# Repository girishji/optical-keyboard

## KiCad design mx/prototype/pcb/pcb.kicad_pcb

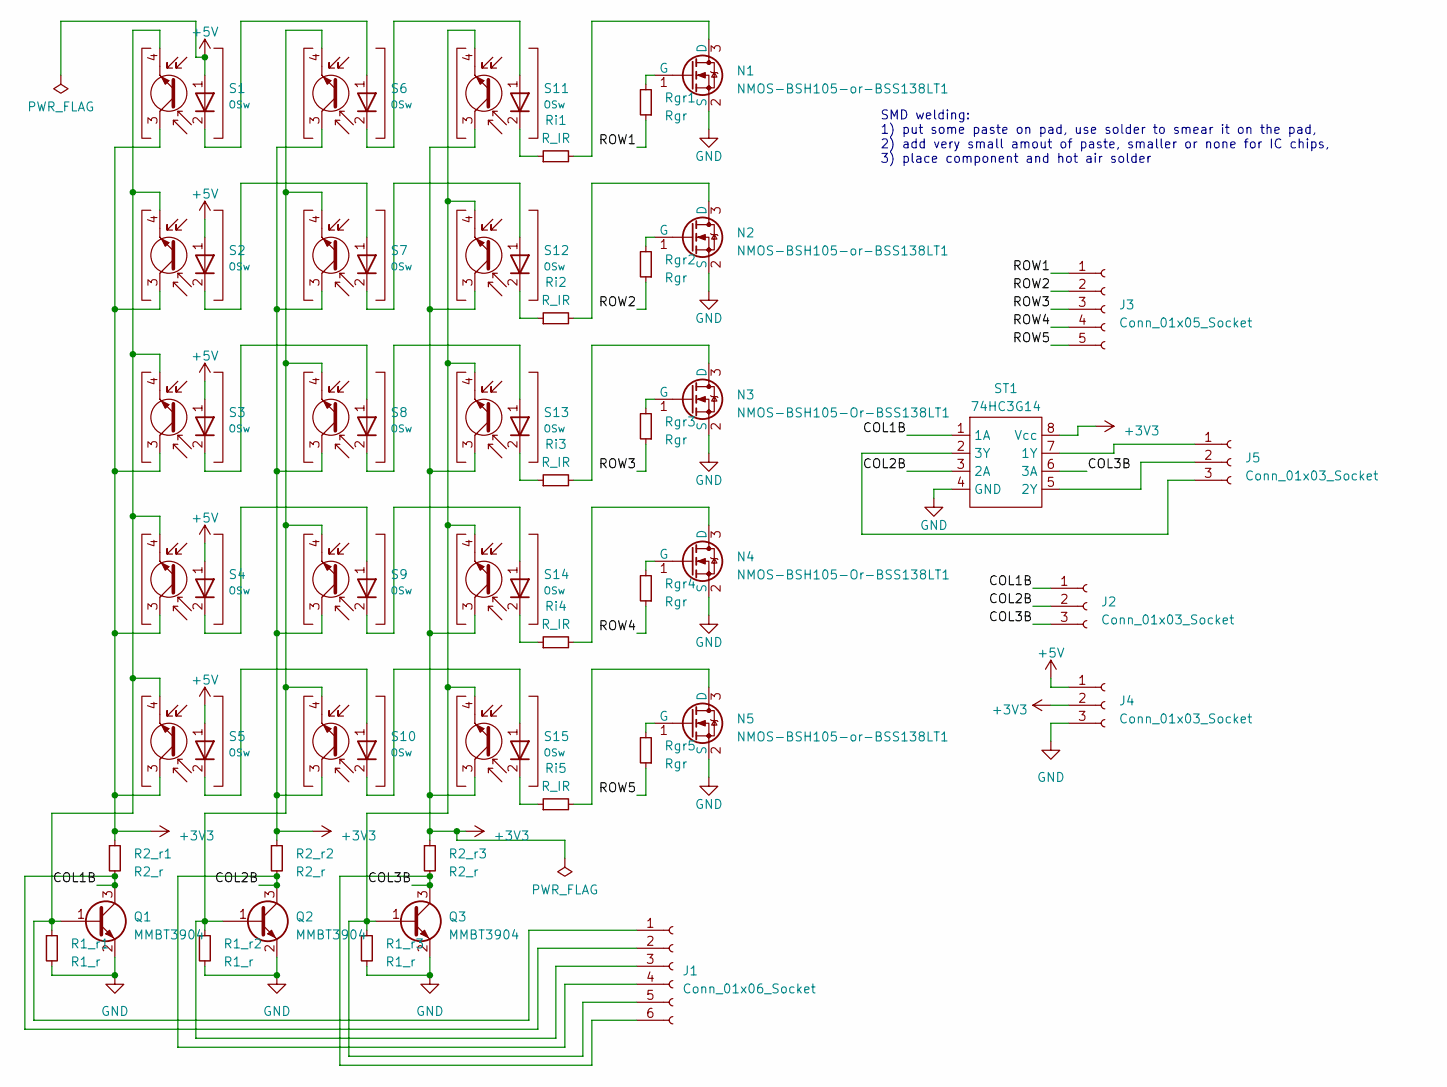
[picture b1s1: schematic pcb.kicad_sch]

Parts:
J1: Conn_01x06_Socket; PinHeader_1x06_P2.54mm_Vertical
J2, J4, J5: Conn_01x03_Socket; PinHeader_1x03_P2.54mm_Vertical
J3: Conn_01x05_Socket; PinHeader_1x05_P2.54mm_Vertical
N1, N2, N5: NMOS-BSH105-or-BSS138LT1; SOT-23-3
N3, N4: NMOS-BSH105-Or-BSS138LT1; SOT-23-3
Q1, Q2, Q3: MMBT3904; SOT-23
R1_r1, R1_r2, R1_r3: R1_r; R_0603_1608Metric; Power Rating 62.5mW; MPN RC0402FR-07160RL; LCSC C327369
R2_r1, R2_r2, R2_r3: R2_r; R_0603_1608Metric; Power Rating 62.5mW; MPN RC0402FR-07160RL; LCSC C327369
Rgr1, Rgr2, Rgr3, Rgr4, Rgr5: Rgr; R_0603_1608Metric; Power Rating 62.5mW; MPN RC0402FR-07160RL; LCSC C327369
Ri1, Ri2, Ri3, Ri4, Ri5: R_IR; R_0603_1608Metric
S1, S2, S3, S4, S5, S6, S7, S8, S9, S10, S11, S12, S13, S14, S15: OSw; Gateron_Sw_1u
ST1: 74HC3G14; TSSOP-8_3x3mm_P0.65mm

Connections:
+3V3: J4.2, R2_r1.1, R2_r2.1, R2_r3.1, S1.3 (C), S2.3 (C), S3.3 (C), S4.3 (C), S5.3 (C), S6.3 (C), S7.3 (C), S8.3 (C), S9.3 (C), S10.3 (C), S11.3 (C), S12.3 (C), S13.3 (C), S14.3 (C), S15.3 (C), ST1.8 (Vcc)
+5V: J4.1, S1.1 (IR_A), S2.1 (IR_A), S3.1 (IR_A), S4.1 (IR_A), S5.1 (IR_A)
/COL1B: J1.2, J2.1, Q1.3 (C), R2_r1.2, ST1.1 (1A)
/COL2B: J1.4, J2.2, Q2.3 (C), R2_r2.2, ST1.3 (2A)
/COL3B: J1.6, J2.3, Q3.3 (C), R2_r3.2, ST1.6 (3A)
/ROW1: J3.1, Rgr1.1
/ROW2: J3.2, Rgr2.1
/ROW3: J3.3, Rgr3.1
/ROW4: J3.4, Rgr4.1
/ROW5: J3.5, Rgr5.1
GND: J4.3, N1.2 (S), N2.2 (S), N3.2 (S), N4.2 (S), N5.2 (S), Q1.2 (E), Q2.2 (E), Q3.2 (E), R1_r1.2, R1_r2.2, R1_r3.2, ST1.4 (GND)
unnamed: J1.1, Q1.1 (B), R1_r1.1, S1.4 (E), S2.4 (E), S3.4 (E), S4.4 (E), S5.4 (E)
unnamed: J1.3, Q2.1 (B), R1_r2.1, S6.4 (E), S7.4 (E), S8.4 (E), S9.4 (E), S10.4 (E)
unnamed: J1.5, Q3.1 (B), R1_r3.1, S11.4 (E), S12.4 (E), S13.4 (E), S14.4 (E), S15.4 (E)
unnamed: J5.1, ST1.7 (1Y)
unnamed: J5.2, ST1.5 (2Y)
unnamed: J5.3, ST1.2 (3Y)
unnamed: N1.3 (D), Ri1.2
unnamed: N1.1 (G), Rgr1.2
unnamed: N2.3 (D), Ri2.2
unnamed: N2.1 (G), Rgr2.2
unnamed: N3.3 (D), Ri3.2
unnamed: N3.1 (G), Rgr3.2
unnamed: N4.3 (D), Ri4.2
unnamed: N4.1 (G), Rgr4.2
unnamed: N5.3 (D), Ri5.2
unnamed: N5.1 (G), Rgr5.2
unnamed: S1.2 (IR_K), S6.1 (IR_A)
unnamed: S2.2 (IR_K), S7.1 (IR_A)
unnamed: S3.2 (IR_K), S8.1 (IR_A)
unnamed: S4.2 (IR_K), S9.1 (IR_A)
unnamed: S5.2 (IR_K), S10.1 (IR_A)
unnamed: S10.2 (IR_K), S15.1 (IR_A)
unnamed: S6.2 (IR_K), S11.1 (IR_A)
unnamed: Ri1.1, S11.2 (IR_K)
unnamed: S7.2 (IR_K), S12.1 (IR_A)
unnamed: Ri2.1, S12.2 (IR_K)
unnamed: S8.2 (IR_K), S13.1 (IR_A)
unnamed: Ri3.1, S13.2 (IR_K)
unnamed: S9.2 (IR_K), S14.1 (IR_A)
unnamed: Ri4.1, S14.2 (IR_K)
unnamed: Ri5.1, S15.2 (IR_K)

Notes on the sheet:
SMD welding: 1) put some paste on pad, use solder to smear it on the pad, 2) add very small amout of paste, smaller or none for IC chips, 3) place component and hot air solder

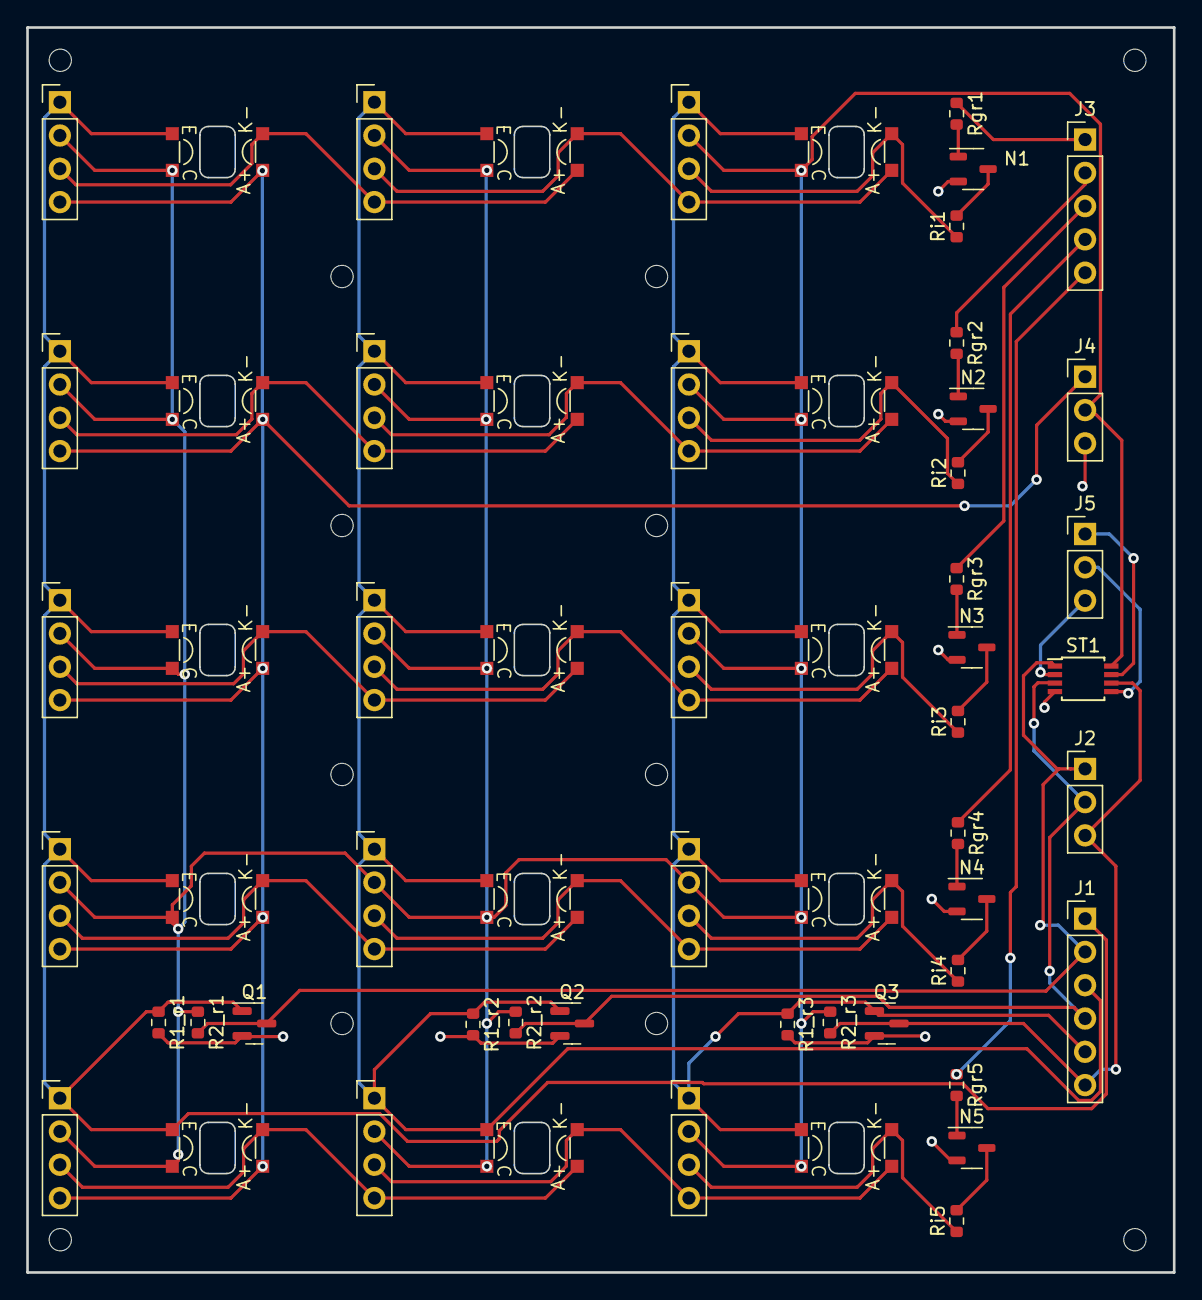
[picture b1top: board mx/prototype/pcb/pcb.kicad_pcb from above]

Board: 2 copper layers, 87.5 x 95.0 mm, 45 parts (0 on the bottom side), 42 nets.

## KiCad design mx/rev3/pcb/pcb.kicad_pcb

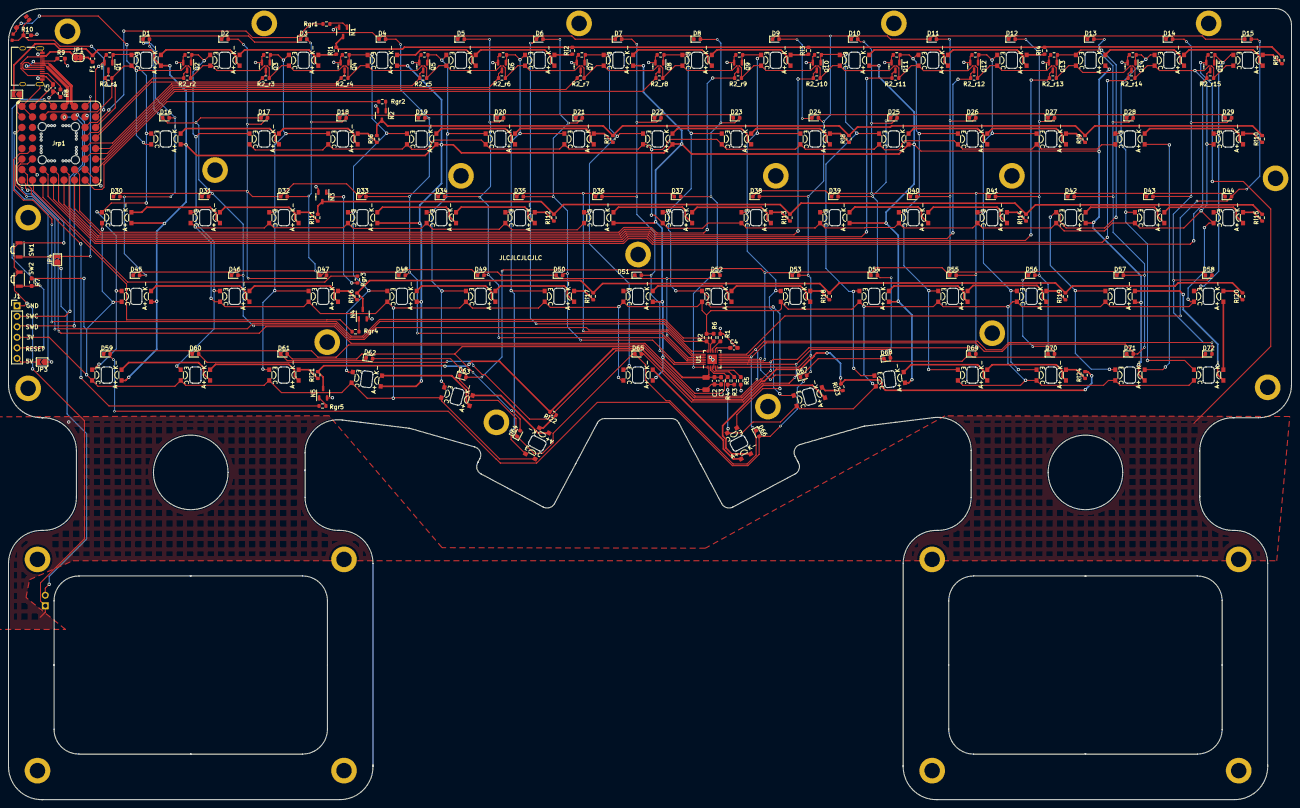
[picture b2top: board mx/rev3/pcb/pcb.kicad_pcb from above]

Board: 2 copper layers, 309.8 x 191.0 mm, 279 parts (0 on the bottom side), 159 nets.

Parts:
Ba1: Conn_01x02_Socket; PinHeader_1x02_P2.54mm_Vertical
C1: 10uF; C_1206_3216Metric
C2: 10uF; C_0603_1608Metric_Pad1.08x0.95mm_HandSolder
C3, C4: 100nF; C_0603_1608Metric_Pad1.08x0.95mm_HandSolder
C5: 2.2uF; C_0603_1608Metric_Pad1.08x0.95mm_HandSolder
D1, D2, D3, D4, D5, D6, D7, D8, D9, D10, D11, D12, D13, D14, D15, D16, D17, D18, D19, D20, D21, D22, D23, D24, D25, D26, D27, D28, D29, D30, D31, D32, D33, D34, D35, D36, D37, D38, D39, D40, D41, D42, D43, D44, D45, D46, D47, D48, D49, D50, D51, D52, D53, D54, D55, D56, D57, D58, D59, D60, D61, D62, D63, D64, D65, D66, D67, D68, D69, D70, D71, D72: LED; LED_0603_1608Metric
F1: 500ma; Fuse_0603_1608Metric
H1, H2, H3, H4, H5, H6, H7, H8: MountingHole; SMTSO_M2
Hs1, Hs2, Hs3, Hs4, Hs5, Hs6, Hs7, Hs8, Hs9, Hs10, Hs11, Hs12, Hs13, Hs14, Hs15, Hs16, Hs17, Hs18: SMTSO_M2
J1: Conn_01x06_Socket; Debug_PinHeader_1x06_P2.54mm_Vertical
JLC1: JLC_Order_Num
JP1: SolderJumper_2_Bridged; SolderJumper-2_P1.3mm_Bridged2Bar_RoundedPad1.0x1.5mm
JP2, JP3, JP4: SolderJumper_2_Open; SolderJumper-2_P1.3mm_Open_TrianglePad1.0x1.5mm
Jrp1: PGA2040; PGA2040_SMT_NO_SLOT
Jusb1: USB_TYPE_C_Receptacle_16P; USB_C_Receptacle_XKB_U262-16XN-4BVC11
N1, N2, N3, N4, N5: N-MOSFET-BSS138LT1; SOT-23-3
Q1, Q2, Q3, Q4, Q5, Q6, Q7, Q8, Q9, Q10, Q11, Q12, Q13, Q14, Q15: MMBT3904; SOT-23
R1, R2, R3: 4.7k; R_0603_1608Metric_Pad0.98x0.95mm_HandSolder
R1_r1, R1_r2, R1_r3, R1_r4, R1_r5, R1_r6, R1_r7, R1_r8, R1_r9, R1_r10, R1_r11, R1_r12, R1_r13, R1_r14, R1_r15: R1_r; R_0603_1608Metric
R2_r1, R2_r2, R2_r3, R2_r4, R2_r5, R2_r6, R2_r7, R2_r8, R2_r9, R2_r10, R2_r11, R2_r12, R2_r13, R2_r14, R2_r15: R2_r; R_0603_1608Metric
R4, R5, R6: 20k; R_0603_1608Metric_Pad0.98x0.95mm_HandSolder
R7, R10: 10k; R_0603_1608Metric_Pad0.98x0.95mm_HandSolder
R8, R9: 5.1k; R_0603_1608Metric_Pad0.98x0.95mm_HandSolder
Rgr1, Rgr2, Rgr3, Rgr4, Rgr5: Rgr; R_0603_1608Metric
Ri1, Ri2, Ri3, Ri4, Ri5, Ri6, Ri7, Ri8, Ri9, Ri10, Ri11, Ri12, Ri13, Ri14, Ri15, Ri16, Ri17, Ri18, Ri19, Ri20, Ri21, Ri22, Ri23, Ri24: R_IR; R_0603_1608Metric
S1, S2, S3, S4, S5, S6, S7, S8, S9, S10, S11, S12, S13, S14, S15, S16, S17, S18, S19, S20, S21, S22, S23, S24, S25, S26, S27, S28, S29, S30, S31, S32, S33, S34, S35, S36, S37, S38, S39, S40, S41, S42, S43, S44, S45, S46, S47, S48, S49, S50, S51, S52, S53, S54, S55, S56, S57, S58, S59, S60, S61, S62, S65, S67, S68, S69, S70, S71, S72: OSw; Gateron_1u_v2
S63: OSw; Gateron_1.25u_v2
S64, S66: OSw; Gateron_2u_v2
SW1, SW2: SW_DIP_x01_XKB_TS_2030; SW_B3U-3000P
Sens1: ALS-PT19
Sens2: TEMT6000-sensor
U1: IS31FL3731-QF; QFN-28-1EP_4x4mm_P0.4mm_EP2.3x2.3mm

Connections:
+3V3: J1.4, Jrp1.B3 (3V3), R1.1, R2.1, R2_r1.1, R2_r2.1, R2_r3.1, R2_r4.1, R2_r5.1, R2_r6.1, R2_r7.1, R2_r8.1, R2_r9.1, R2_r10.1, R2_r11.1, R2_r12.1, R2_r13.1, R2_r14.1, R2_r15.1, R3.1, R4.1, R7.1, S1.3 (C), S2.3 (C), S3.3 (C), S4.3 (C), S5.3 (C), S6.3 (C), S7.3 (C), S8.3 (C), S9.3 (C), S10.3 (C), S11.3 (C), S12.3 (C), S13.3 (C), S14.3 (C), S15.3 (C), S16.3 (C), S17.3 (C), S18.3 (C), S19.3 (C), S20.3 (C), S21.3 (C), S22.3 (C), S23.3 (C), S24.3 (C), S25.3 (C), S26.3 (C), S27.3 (C), S28.3 (C), S29.3 (C), S30.3 (C), S31.3 (C), S32.3 (C), S33.3 (C), S34.3 (C), S35.3 (C), S36.3 (C), S37.3 (C), S38.3 (C), S39.3 (C), S40.3 (C), S41.3 (C), S42.3 (C), S43.3 (C), S44.3 (C), S45.3 (C), S46.3 (C), S47.3 (C), S48.3 (C), S49.3 (C), S50.3 (C), S51.3 (C), S52.3 (C), S53.3 (C), S54.3 (C), S55.3 (C), S56.3 (C), S57.3 (C), S58.3 (C), S59.3 (C), S60.3 (C), S61.3 (C), S62.3 (C), S63.3 (C), S64.3 (C), S65.3 (C), S66.3 (C), S67.3 (C), S68.3 (C), S69.3 (C), S70.3 (C), S71.3 (C), S72.3 (C), Sens1.1 (C), Sens2.1 (C)
+5V: C1.2, C2.1, C3.1, F1.2, JP2.2 (B), S1.1 (IR_A), S4.1 (IR_A), S7.1 (IR_A), S10.1 (IR_A), S13.1 (IR_A), S16.1 (IR_A), S19.1 (IR_A), S22.1 (IR_A), S25.1 (IR_A), S30.1 (IR_A), S33.1 (IR_A), S36.1 (IR_A), S39.1 (IR_A), S42.1 (IR_A), S45.1 (IR_A), S48.1 (IR_A), S51.1 (IR_A), S54.1 (IR_A), S57.1 (IR_A), S59.1 (IR_A), S62.1 (IR_A), S65.1 (IR_A), S68.1 (IR_A), S71.1 (IR_A), U1.2 (VCC)
/AD: R6.1, U1.18 (AD)
/COL1: Jrp1.C8 (GPIO27/ADC1), Q1.3 (C), R2_r1.2
/COL2: Jrp1.D7 (GPIO26/ADC0), Q2.3 (C), R2_r2.2
/COL3: Jrp1.D8 (GPIO25), Q3.3 (C), R2_r3.2
/COL4: Jrp1.E7 (GPIO24), Q4.3 (C), R2_r4.2
/COL5: Jrp1.E8 (GPIO23), Q5.3 (C), R2_r5.2
/COL6: Jrp1.F7 (GPIO22), Q6.3 (C), R2_r6.2
/COL7: Jrp1.F8 (GPIO21), Q7.3 (C), R2_r7.2
/COL8: Jrp1.G8 (GPIO20), Q8.3 (C), R2_r8.2
/COL9: Jrp1.G6 (GPIO18), Q9.3 (C), R2_r9.2
/COL10: Jrp1.H6 (GPIO17), Q10.3 (C), R2_r10.2
/COL11: Jrp1.G5 (GPIO16), Q11.3 (C), R2_r11.2
/COL12: Jrp1.H5 (GPIO15), Q12.3 (C), R2_r12.2
/COL13: Jrp1.G4 (GPIO14), Q13.3 (C), R2_r13.2
/COL14: Jrp1.H4 (GPIO13), Q14.3 (C), R2_r14.2
/COL15: Jrp1.G3 (GPIO12), Q15.3 (C), R2_r15.2
/C_FLT: C4.1, U1.16 (C_FILT)
/R1_SINK: N1.3 (D), Ri1.2, Ri2.2, Ri3.2, Ri4.2, Ri5.2
/R2_SINK: N2.3 (D), Ri6.2, Ri7.2, Ri8.2, Ri9.2, Ri10.2
/R3_SINK: N3.3 (D), Ri11.2, Ri12.2, Ri13.2, Ri14.2, Ri15.2
/R4_SINK: N4.3 (D), Ri16.2, Ri17.2, Ri18.2, Ri19.2, Ri20.2
/R5_SINK: N5.3 (D), Ri21.2, Ri22.2, Ri23.2, Ri24.2
/ROW1: Jrp1.C7 (GPIO28/ADC2), Rgr1.1
/ROW2: Jrp1.H7 (GPIO19), Rgr2.1
/ROW3: Jrp1.H3 (GPIO11), Rgr3.1
/ROW4: Jrp1.H2 (GPIO10), Rgr4.1
/ROW5: Jrp1.G1 (GPIO9), Rgr5.1
/RUN: J1.5, Jrp1.A4 (RUN), R7.2, SW2.2
/R_EXT: R5.1, U1.6 (R_EXT)
/USB_D+: Jrp1.A5 (USB_DP), Jusb1.A6 (D1+), Jusb1.B6 (D2+)
/USB_D-: Jrp1.A6 (USB_DM), Jusb1.A7 (D1-), Jusb1.B7 (D2-)
/~INTB: R3.2, U1.4 (~INTB)
/~SDB: Jrp1.F2 (GPIO8), R4.2, U1.3 (~SDB)
/~USB_BOOT: JP4.2 (B), Jrp1.A7 (BOOTSEL), SW1.2
BATT: Ba1.2, JP4.1 (A)
CA1: D1.1 (K), D2.1 (K), D3.1 (K), D4.1 (K), D5.1 (K), D6.1 (K), D7.1 (K), D8.1 (K), D16.2 (A), D30.2 (A), D45.2 (A), U1.21 (CA1)
CA2: D1.2 (A), D16.1 (K), D17.1 (K), D18.1 (K), D19.1 (K), D20.1 (K), D21.1 (K), D22.1 (K), D23.1 (K), D31.2 (A), D46.2 (A), U1.22 (CA2)
CA3: D2.2 (A), D17.2 (A), D30.1 (K), D31.1 (K), D32.1 (K), D33.1 (K), D34.1 (K), D35.1 (K), D36.1 (K), D37.1 (K), D47.2 (A), U1.23 (CA3)
CA4: D3.2 (A), D18.2 (A), D32.2 (A), D45.1 (K), D46.1 (K), D47.1 (K), D48.1 (K), D49.1 (K), D50.1 (K), D51.1 (K), D52.1 (K), U1.24 (CA4)
CA5: D4.2 (A), D19.2 (A), D33.2 (A), D48.2 (A), U1.25 (CA5)
CA6: D5.2 (A), D20.2 (A), D34.2 (A), D49.2 (A), U1.26 (CA6)
CA7: D6.2 (A), D21.2 (A), D35.2 (A), D50.2 (A), U1.27 (CA7)
CA8: D7.2 (A), D22.2 (A), D36.2 (A), D51.2 (A), U1.28 (CA8)
CA9: D8.2 (A), D23.2 (A), D37.2 (A), D52.2 (A), U1.1 (CA9)
CB1: D9.1 (K), D10.1 (K), D11.1 (K), D12.1 (K), D13.1 (K), D14.1 (K), D15.1 (K), D24.2 (A), D38.2 (A), D53.2 (A), D59.2 (A), D66.2 (A), D67.2 (A), U1.7 (CB1)
CB2: D9.2 (A), D24.1 (K), D25.1 (K), D26.1 (K), D27.1 (K), D28.1 (K), D29.1 (K), D39.2 (A), D54.2 (A), D60.2 (A), D65.2 (A), D68.2 (A), U1.8 (CB2)
CB3: D10.2 (A), D25.2 (A), D38.1 (K), D39.1 (K), D40.1 (K), D41.1 (K), D42.1 (K), D43.1 (K), D44.1 (K), D55.2 (A), D61.2 (A), D64.2 (A), D69.2 (A), U1.9 (CB3)
CB4: D11.2 (A), D26.2 (A), D40.2 (A), D53.1 (K), D54.1 (K), D55.1 (K), D56.1 (K), D57.1 (K), D58.1 (K), D62.2 (A), D63.2 (A), D70.2 (A), U1.10 (CB4)
CB5: D12.2 (A), D27.2 (A), D41.2 (A), D56.2 (A), D67.1 (K), D68.1 (K), D69.1 (K), D70.1 (K), D71.1 (K), D72.1 (K), U1.11 (CB5)
CB6: D13.2 (A), D28.2 (A), D42.2 (A), D57.2 (A), D63.1 (K), D64.1 (K), D65.1 (K), D66.1 (K), D71.2 (A), U1.12 (CB6)
CB7: D14.2 (A), D29.2 (A), D43.2 (A), D58.2 (A), D59.1 (K), D60.1 (K), D61.1 (K), D62.1 (K), D72.2 (A), U1.13 (CB7)
CB8: D15.2 (A), D44.2 (A), U1.14 (CB8)
GND: Ba1.1, C1.1, C2.2, C3.2, C4.2, C5.1, J1.1, Jrp1.A1 (GND), Jrp1.A8 (GND), Jrp1.B2 (GND), Jrp1.B7 (GND), Jrp1.G2 (GND), Jrp1.G7 (GND), Jrp1.H1 (GND), Jrp1.H8 (GND), Jusb1.A1 (GND), Jusb1.A12 (GND), Jusb1.B1 (GND), Jusb1.B12 (GND), Jusb1.S1 (SHIELD), N1.2 (S), N2.2 (S), N3.2 (S), N4.2 (S), N5.2 (S), Q1.2 (E), Q2.2 (E), Q3.2 (E), Q4.2 (E), Q5.2 (E), Q6.2 (E), Q7.2 (E), Q8.2 (E), Q9.2 (E), Q10.2 (E), Q11.2 (E), Q12.2 (E), Q13.2 (E), Q14.2 (E), Q15.2 (E), R1_r1.2, R1_r2.2, R1_r3.2, R1_r4.2, R1_r5.2, R1_r6.2, R1_r7.2, R1_r8.2, R1_r9.2, R1_r10.2, R1_r11.2, R1_r12.2, R1_r13.2, R1_r14.2, R1_r15.2, R5.2, R6.2, R8.2, R9.2, R10.2, SW1.1, SW2.1, U1.5 (GND), U1.29 (GND)
unnamed: F1.1, JP1.2 (B)
unnamed: JP2.1 (A), Jrp1.B1 (GPIO0)
unnamed: JP3.1 (A), Jrp1.C1 (GPIO1)
unnamed: Jusb1.A5 (CC1), R9.1
unnamed: Jusb1.B5 (CC2), R8.1
unnamed: N1.1 (G), Rgr1.2
unnamed: N2.1 (G), Rgr2.2
unnamed: N3.1 (G), Rgr3.2
unnamed: N4.1 (G), Rgr4.2
unnamed: N5.1 (G), Rgr5.2
unnamed: Q1.1 (B), R1_r1.1, S1.4 (E), S16.4 (E), S30.4 (E), S45.4 (E), S59.4 (E)
unnamed: Q2.1 (B), R1_r2.1, S2.4 (E), S17.4 (E), S31.4 (E), S46.4 (E), S60.4 (E)
unnamed: Q3.1 (B), R1_r3.1, S3.4 (E), S18.4 (E), S32.4 (E), S47.4 (E), S61.4 (E)
unnamed: Q4.1 (B), R1_r4.1, S4.4 (E), S19.4 (E), S33.4 (E), S48.4 (E), S62.4 (E)
unnamed: Q5.1 (B), R1_r5.1, S5.4 (E), S20.4 (E), S34.4 (E), S49.4 (E), S63.4 (E)
unnamed: Q6.1 (B), R1_r6.1, S6.4 (E), S21.4 (E), S35.4 (E), S50.4 (E), S64.4 (E)
unnamed: Q7.1 (B), R1_r7.1, S7.4 (E), S22.4 (E), S36.4 (E), S51.4 (E), S65.4 (E)
unnamed: Q8.1 (B), R1_r8.1, S8.4 (E), S23.4 (E), S37.4 (E), S52.4 (E), S66.4 (E)
unnamed: Q9.1 (B), R1_r9.1, S9.4 (E), S24.4 (E), S38.4 (E), S53.4 (E), S67.4 (E)
unnamed: Q10.1 (B), R1_r10.1, S10.4 (E), S25.4 (E), S39.4 (E), S54.4 (E), S68.4 (E)
unnamed: Q11.1 (B), R1_r11.1, S11.4 (E), S26.4 (E), S40.4 (E), S55.4 (E), S69.4 (E)
unnamed: Q12.1 (B), R1_r12.1, S12.4 (E), S27.4 (E), S41.4 (E), S56.4 (E), S70.4 (E)
unnamed: Q13.1 (B), R1_r13.1, S13.4 (E), S42.4 (E), S57.4 (E), S71.4 (E)
unnamed: Q14.1 (B), R1_r14.1, S14.4 (E), S28.4 (E), S43.4 (E), S72.4 (E)
unnamed: Q15.1 (B), R1_r15.1, S15.4 (E), S29.4 (E), S44.4 (E), S58.4 (E)
unnamed: S1.2 (IR_K), S2.1 (IR_A)
unnamed: S2.2 (IR_K), S3.1 (IR_A)
unnamed: Ri1.1, S3.2 (IR_K)
unnamed: S4.2 (IR_K), S5.1 (IR_A)
unnamed: S5.2 (IR_K), S6.1 (IR_A)
unnamed: Ri2.1, S6.2 (IR_K)
unnamed: S7.2 (IR_K), S8.1 (IR_A)
unnamed: S8.2 (IR_K), S9.1 (IR_A)
unnamed: Ri3.1, S9.2 (IR_K)
unnamed: S10.2 (IR_K), S11.1 (IR_A)
unnamed: S11.2 (IR_K), S12.1 (IR_A)
unnamed: Ri4.1, S12.2 (IR_K)
unnamed: S13.2 (IR_K), S14.1 (IR_A)
unnamed: S14.2 (IR_K), S15.1 (IR_A)
unnamed: Ri5.1, S15.2 (IR_K)
unnamed: S16.2 (IR_K), S17.1 (IR_A)
unnamed: S17.2 (IR_K), S18.1 (IR_A)
unnamed: Ri6.1, S18.2 (IR_K)
unnamed: S19.2 (IR_K), S20.1 (IR_A)
unnamed: S20.2 (IR_K), S21.1 (IR_A)
unnamed: Ri7.1, S21.2 (IR_K)
unnamed: S22.2 (IR_K), S23.1 (IR_A)
unnamed: S23.2 (IR_K), S24.1 (IR_A)
unnamed: Ri8.1, S24.2 (IR_K)
unnamed: S25.2 (IR_K), S26.1 (IR_A)
unnamed: S26.2 (IR_K), S27.1 (IR_A)
unnamed: Ri9.1, S27.2 (IR_K)
unnamed: S28.1 (IR_A), S71.2 (IR_K)
unnamed: S28.2 (IR_K), S29.1 (IR_A)
unnamed: Ri10.1, S29.2 (IR_K)
unnamed: S30.2 (IR_K), S31.1 (IR_A)
unnamed: S31.2 (IR_K), S32.1 (IR_A)
unnamed: Ri11.1, S32.2 (IR_K)
unnamed: S33.2 (IR_K), S34.1 (IR_A)
unnamed: S34.2 (IR_K), S35.1 (IR_A)
unnamed: Ri12.1, S35.2 (IR_K)
unnamed: S36.2 (IR_K), S37.1 (IR_A)
unnamed: S37.2 (IR_K), S38.1 (IR_A)
unnamed: Ri13.1, S38.2 (IR_K)
unnamed: S39.2 (IR_K), S40.1 (IR_A)
unnamed: S40.2 (IR_K), S41.1 (IR_A)
unnamed: Ri14.1, S41.2 (IR_K)
unnamed: S42.2 (IR_K), S43.1 (IR_A)
unnamed: S43.2 (IR_K), S44.1 (IR_A)
unnamed: Ri15.1, S44.2 (IR_K)
unnamed: S45.2 (IR_K), S46.1 (IR_A)
unnamed: S46.2 (IR_K), S47.1 (IR_A)
unnamed: Ri16.1, S47.2 (IR_K)
unnamed: S48.2 (IR_K), S49.1 (IR_A)
unnamed: S49.2 (IR_K), S50.1 (IR_A)
unnamed: Ri17.1, S50.2 (IR_K)
unnamed: S51.2 (IR_K), S52.1 (IR_A)
unnamed: S52.2 (IR_K), S53.1 (IR_A)
unnamed: Ri18.1, S53.2 (IR_K)
unnamed: S54.2 (IR_K), S55.1 (IR_A)
unnamed: S55.2 (IR_K), S56.1 (IR_A)
unnamed: Ri19.1, S56.2 (IR_K)
unnamed: S57.2 (IR_K), S72.1 (IR_A)
unnamed: S58.1 (IR_A), S72.2 (IR_K)
unnamed: Ri20.1, S58.2 (IR_K)
unnamed: S59.2 (IR_K), S60.1 (IR_A)
unnamed: S60.2 (IR_K), S61.1 (IR_A)
unnamed: Ri21.1, S61.2 (IR_K)
unnamed: S62.2 (IR_K), S63.1 (IR_A)
unnamed: S63.2 (IR_K), S64.1 (IR_A)
unnamed: Ri22.1, S64.2 (IR_K)
unnamed: S65.2 (IR_K), S66.1 (IR_A)
unnamed: S66.2 (IR_K), S67.1 (IR_A)
unnamed: Ri23.1, S67.2 (IR_K)
unnamed: S68.2 (IR_K), S69.1 (IR_A)
unnamed: S69.2 (IR_K), S70.1 (IR_A)
unnamed: Ri24.1, S70.2 (IR_K)
SCL: Jrp1.F1 (GPIO7), R2.2, U1.20 (SCL)
SDA: Jrp1.E2 (GPIO6), R1.2, U1.19 (SDA)
SENSOR: Jrp1.B8 (GPIO29/ADC3), R10.1, Sens1.2 (E), Sens2.2 (E)
SWCLK: J1.2, Jrp1.B5 (SWCLK)
SWDIO: J1.3, Jrp1.B6 (SWDIO)
VBUS: C5.2, JP1.1 (A), Jrp1.A2 (VBUS), Jusb1.A4 (VBUS), Jusb1.A9 (VBUS), Jusb1.B4 (VBUS), Jusb1.B9 (VBUS)
VDDH: J1.6, JP3.2 (B)

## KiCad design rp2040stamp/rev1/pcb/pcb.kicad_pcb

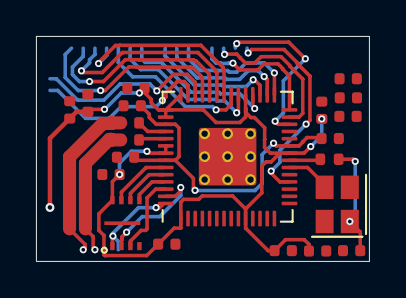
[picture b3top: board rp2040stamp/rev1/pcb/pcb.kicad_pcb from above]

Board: 2 copper layers, 18.5 x 12.5 mm, 23 parts (0 on the bottom side), 35 nets.

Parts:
C1, C2, C3, C4, C5, C6, C7, C8, C9, C12: 100nF; C_0402_1005Metric
C10, C11: 1uF; C_0402_1005Metric
C13: 2.2uF; C_0402_1005Metric
C14, C15: 15pF; C_0402_1005Metric
DB1: MINEW-MS88SF3; MINEW-MS88SF3-Daughter-Board
JLC1: JLC_Order_Num
R1, R2: 27R; R_0402_1005Metric
R3: 1k; R_0402_1005Metric
U1: RP2040; RP2040-QFN-56
U2: Memory_Flash_W25Q64_XSON; 8-USON-Handsolder
X1: 12.000MHz; Crystal_SMD_2520-4Pin_2.5x2.0mm-Handsolder

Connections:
+1V1: C1.1, C2.1, C10.1, U1.23 (DVDD), U1.45 (VREG_VOUT), U1.50 (DVDD)
+3V3: C3.1, C4.1, C5.1, C6.1, C7.1, C8.1, C9.1, C11.1, C12.1, C13.1, DB1.31 (VDD), U1.1 (IOVDD), U1.10 (IOVDD), U1.22 (IOVDD), U1.33 (IOVDD), U1.42 (IOVDD), U1.43 (ADC_AVDD), U1.44 (VREG_IN), U1.48 (USB_VDD), U1.49 (IOVDD), U2.8 (VCC)
/D+: R1.1, U1.47 (USB_DP)
/D-: R2.1, U1.46 (USB_DM)
/GPIO0: DB1.40 (P0.15), U1.2 (GPIO0)
/GPIO15: DB1.2 (P1.11), U1.18 (GPIO15)
/GPIO18: DB1.7 (P1.13), U1.29 (GPIO18)
/GPIO19: DB1.8 (P1.15), U1.30 (GPIO19)
/GPIO20: DB1.9 (P0.02-AIN0), U1.31 (GPIO20)
/GPIO21: DB1.11 (P0.28-AIN4), U1.32 (GPIO21)
/GPIO22: DB1.12 (P0.30-AIN6), U1.34 (GPIO22)
/GPIO23: DB1.13 (P0.31-AIN7), U1.35 (GPIO23)
/GPIO24: DB1.14 (P0.27), U1.36 (GPIO24)
/GPIO25: DB1.15 (P0.05-AIN3), U1.37 (GPIO25)
/GPIO26: DB1.16 (P0.04-AIN2), U1.38 (GPIO26_ADC0)
/GPIO27: DB1.17 (P0.26), U1.39 (GPIO27_ADC1)
/GPIO28: DB1.20 (P0.06), U1.40 (GPIO28_ADC2)
/GPIO29: DB1.21 (P1.08), U1.41 (GPIO29_ADC3)
/QSPI_SCLK: U1.52 (QSPI_SCLK), U2.6 (CLK)
/QSPI_SD0: U1.53 (QSPI_SD0), U2.5 (DI_(IO0))
/QSPI_SD1: U1.55 (QSPI_SD1), U2.2 (DO_(IO1))
/QSPI_SD2: U1.54 (QSPI_SD2), U2.3 (~WP_(IO2))
/QSPI_SD3: U1.51 (QSPI_SD3), U2.7 (~HOLD_(IO3))
/QSPI_SS: DB1.39 (P0.13), U1.56 (QSPI_SS), U2.1 (~{CS)
/RUN: DB1.3 (P1.12), U1.26 (RUN)
/SWCLK: DB1.50 (SWDCLK), U1.24 (SWCLK)
/SWD: DB1.49 (SWDIO), U1.25 (SWD)
/USB_D+: DB1.37 (D+), R1.2
/USB_D-: DB1.36 (D-), R2.2
/XIN: C15.1, U1.20 (XIN), X1.3
/XOUT: R3.1, U1.21 (XOUT)
GND: C1.2, C2.2, C3.2, C4.2, C5.2, C6.2, C7.2, C8.2, C9.2, C10.2, C11.2, C12.2, C13.2, C14.2, C15.2, DB1.1 (GND), DB1.18 (GND), DB1.34 (GND), DB1.56 (GND), U1.19 (TESTEN), U1.57 (GND), U2.4 (GND), U2.9 (EP), X1.2, X1.4
unnamed: C14.1, R3.2, X1.1
SCL: DB1.5 (P1.14), U1.28 (GPIO17)
SDA: DB1.4 (P1.10), U1.27 (GPIO16)
